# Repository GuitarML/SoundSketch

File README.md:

# SoundSketch

Hardware and software for Soundsketch guitar pedal as shown on [Youtube](https://youtu.be/grorq3XL0zQ?si=FIOID7Fv4AuRCGD6)

Borrows from the open source [DaisySeedProjects](https://github.com/bkshepherd/DaisySeedProjects) pedal, but expression and 3 way toggles, and screen/encoder, midi out removed. 

Not all of the Planet Series software modules ported from Funbox have been tested, some code editing may be required. 

IMPORTANT: When ordering assembled Soundsketch PCBs from JLCPcb or PCBway, you have to manually rotate certain components to the correct orientation on their online tool as part of the ordering process. This is required because the part data exported from KiCad to the .pos file is a different standard from what is expected by the manufacturer. Use the KiCad PCB view to verify correct orientation of ICs and diodes when compared to the manufacturer's parts visualization tool. 

Tayda Drill Template:
https://drill.taydakits.com/box-designs/new?public_key=MndaazFjcjJRM3hIUVQxenhPUm1Rdz09Cg==

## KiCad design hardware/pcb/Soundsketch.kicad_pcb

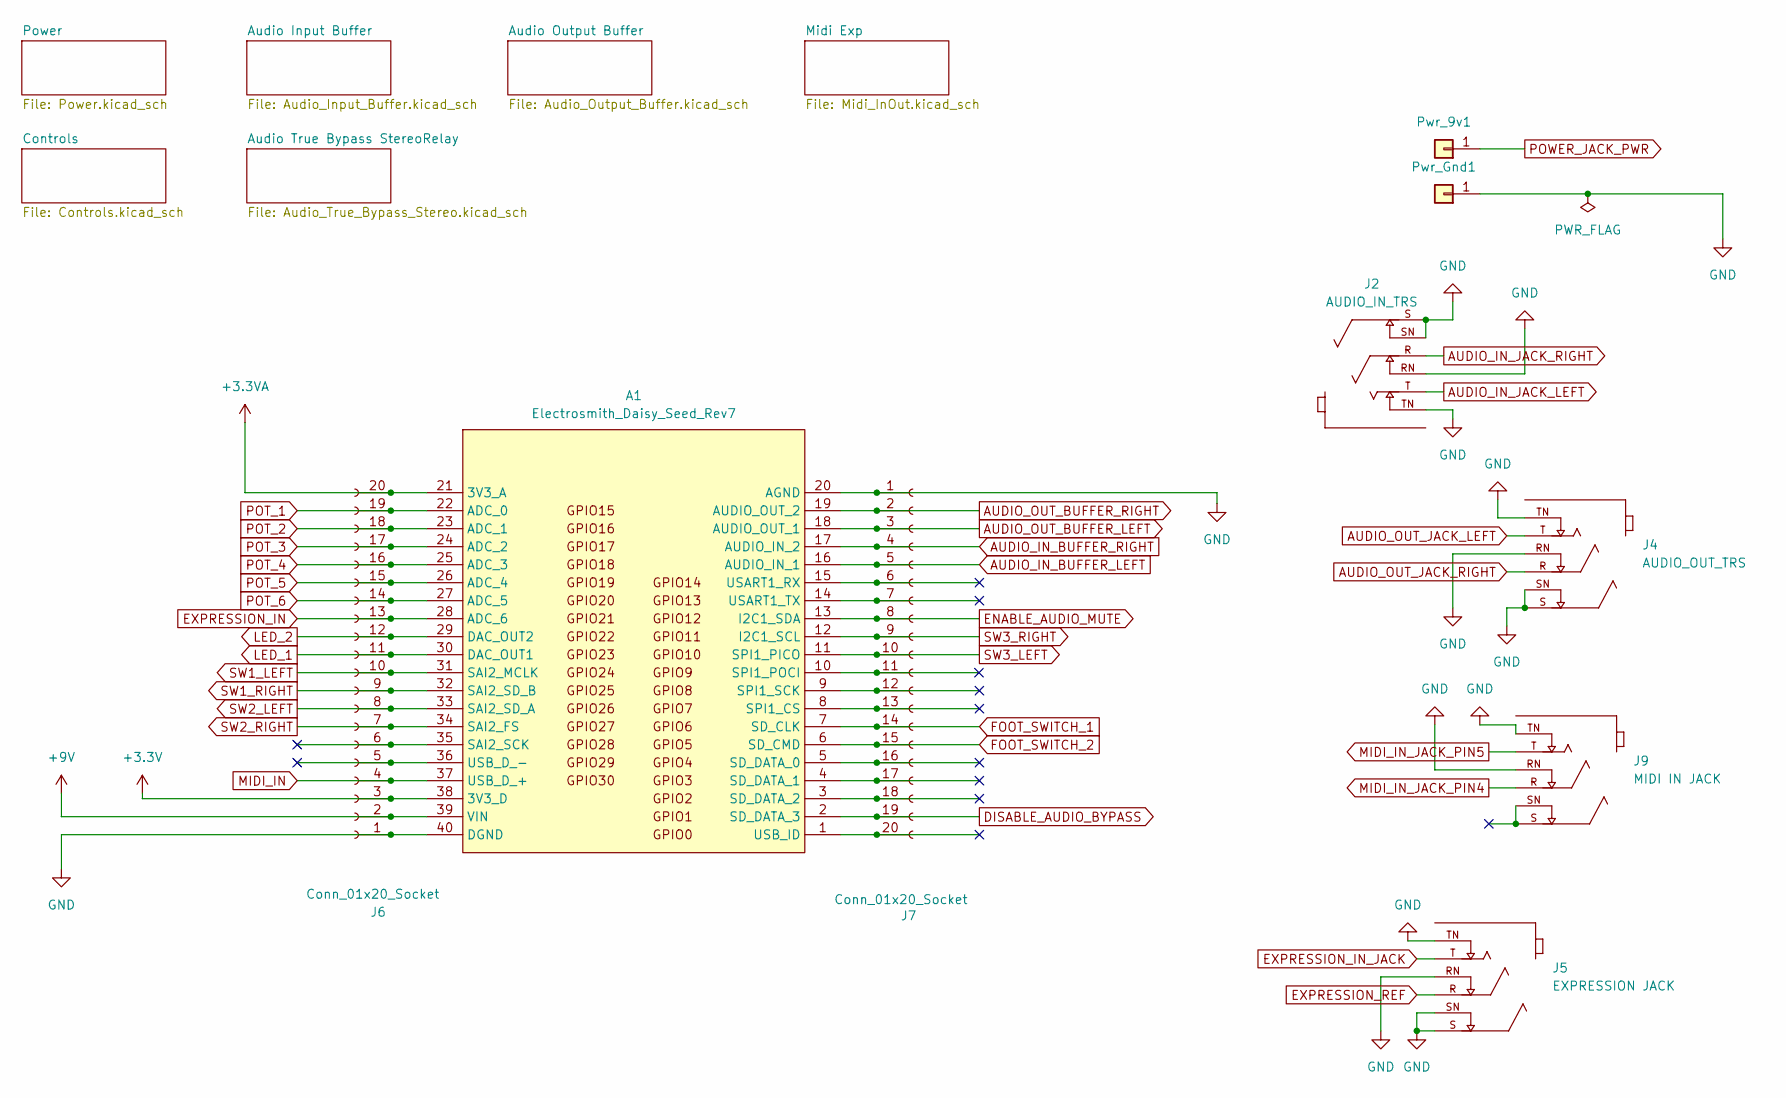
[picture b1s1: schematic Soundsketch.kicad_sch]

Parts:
A1: Electrosmith_Daisy_Seed_Rev7
J2: AUDIO_IN_TRS; NEUTRIK_NMJ6HCD2; PARTREV 26.02.2021
J4: AUDIO_OUT_TRS; NEUTRIK_NMJ6HCD2; PARTREV 26.02.2021
J5: EXPRESSION JACK; NEUTRIK_NMJ6HCD2; PARTREV 26.02.2021
J6, J7: Conn_01x20_Socket; PinSocket1x20_P2.54mm_Vertical_JLCPCB
J9: MIDI IN JACK; NEUTRIK_NMJ6HCD2; PARTREV 26.02.2021
Pwr_9v1: TestPoint_THTPad_D2.0mm_Drill1.0mm
Pwr_Gnd1: TestPoint_THTPad_D2.0mm_Drill1.0mm

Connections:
+3.3V: A1.38 (3V3_D), J6.3; also elsewhere on the board
+3.3VA: A1.21 (3V3_A), J6.20; also elsewhere on the board
+9V: A1.39 (VIN), J6.2; also elsewhere on the board
AUDIO_IN_BUFFER_LEFT: A1.16 (AUDIO_IN_1), J7.5; also elsewhere on the board
AUDIO_IN_BUFFER_RIGHT: A1.17 (AUDIO_IN_2), J7.4; also elsewhere on the board
AUDIO_IN_JACK_LEFT: J2.T; also elsewhere on the board
AUDIO_IN_JACK_RIGHT: J2.R; also elsewhere on the board
AUDIO_OUT_BUFFER_LEFT: A1.18 (AUDIO_OUT_1), J7.3; also elsewhere on the board
AUDIO_OUT_BUFFER_RIGHT: A1.19 (AUDIO_OUT_2), J7.2; also elsewhere on the board
AUDIO_OUT_JACK_LEFT: J4.T; also elsewhere on the board
AUDIO_OUT_JACK_RIGHT: J4.R; also elsewhere on the board
DISABLE_AUDIO_BYPASS: A1.2 (SD_DATA_3), J7.19; also elsewhere on the board
ENABLE_AUDIO_MUTE: A1.13 (I2C1_SDA), J7.8; also elsewhere on the board
EXPRESSION_IN: A1.28 (ADC_6), J6.13; also elsewhere on the board
EXPRESSION_IN_JACK: J5.T; also elsewhere on the board
EXPRESSION_REF: J5.R; also elsewhere on the board
FOOT_SWITCH_1: A1.7 (SD_CLK), J7.14; also elsewhere on the board
FOOT_SWITCH_2: A1.6 (SD_CMD), J7.15; also elsewhere on the board
GND: A1.20 (AGND), A1.40 (DGND), J2.RN, J2.S, J2.SN, J2.TN, J4.RN, J4.S, J4.SN, J4.TN, J5.RN, J5.S, J5.SN, J5.TN, J6.1, J7.1, J9.RN, J9.TN, Pwr_Gnd1.1; also elsewhere on the board
LED_1: A1.30 (DAC_OUT1), J6.11; also elsewhere on the board
LED_2: A1.29 (DAC_OUT2), J6.12; also elsewhere on the board
MIDI_IN: A1.37 (USB_D_+), J6.4; also elsewhere on the board
MIDI_IN_JACK_PIN4: J9.R; also elsewhere on the board
MIDI_IN_JACK_PIN5: J9.T; also elsewhere on the board
unnamed: A1.1 (USB_ID), J7.20
unnamed: A1.3 (SD_DATA_2), J7.18
unnamed: A1.4 (SD_DATA_1), J7.17
unnamed: A1.5 (SD_DATA_0), J7.16
unnamed: A1.8 (SPI1_CS), J7.13
unnamed: A1.9 (SPI1_SCK), J7.12
unnamed: A1.14 (USART1_TX), J7.7
unnamed: A1.15 (USART1_RX), J7.6
unnamed: A1.35 (SAI2_SCK), J6.6
unnamed: A1.36 (USB_D_-), J6.5
unnamed: A1.10 (SPI1_POCI), J7.11
POT_1: A1.22 (ADC_0), J6.19; also elsewhere on the board
POT_2: A1.23 (ADC_1), J6.18; also elsewhere on the board
POT_3: A1.24 (ADC_2), J6.17; also elsewhere on the board
POT_4: A1.25 (ADC_3), J6.16; also elsewhere on the board
POT_5: A1.26 (ADC_4), J6.15; also elsewhere on the board
POT_6: A1.27 (ADC_5), J6.14; also elsewhere on the board
POWER_JACK_PWR: Pwr_9v1.1; also elsewhere on the board
SW1_LEFT: A1.31 (SAI2_MCLK), J6.10; also elsewhere on the board
SW1_RIGHT: A1.32 (SAI2_SD_B), J6.9; also elsewhere on the board
SW2_LEFT: A1.33 (SAI2_SD_A), J6.8; also elsewhere on the board
SW2_RIGHT: A1.34 (SAI2_FS), J6.7; also elsewhere on the board
SW3_LEFT: A1.11 (SPI1_PICO), J7.10; also elsewhere on the board
SW3_RIGHT: A1.12 (I2C1_SCL), J7.9; also elsewhere on the board

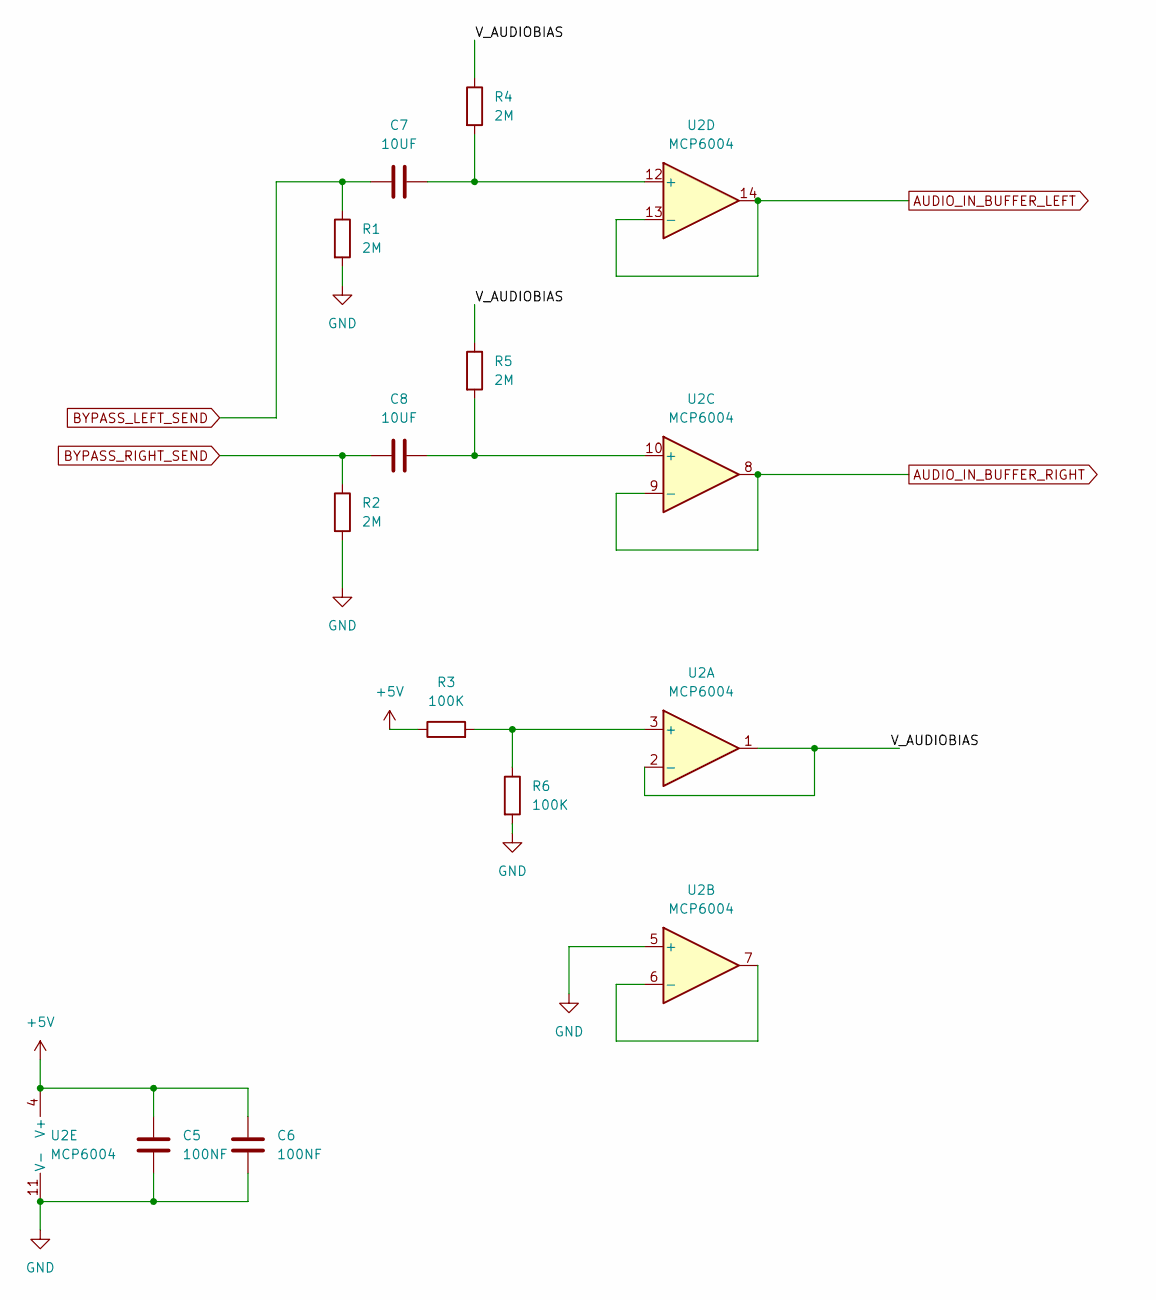
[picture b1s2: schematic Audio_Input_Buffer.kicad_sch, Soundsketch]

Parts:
C5, C6: 100NF; C_0805_2012Metric
C7, C8: 10UF; C_0805_2012Metric
R1, R2, R4, R5: 2M; R_0805_2012Metric
R3, R6: 100K; R_0805_2012Metric
U2: MCP6004; SOIC-14_3.9x8.7mm_P1.27mm

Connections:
+5V: C5.1, C6.1, R3.1, U2.4 (V+); also elsewhere on the board
/Audio Input Buffer/V_AUDIOBIAS: R4.1, R5.1, U2.1, U2.2 (-)
AUDIO_IN_BUFFER_LEFT: U2.13 (-), U2.14; also elsewhere on the board
AUDIO_IN_BUFFER_RIGHT: U2.8, U2.9 (-); also elsewhere on the board
BYPASS_LEFT_SEND: C7.1, R1.1; also elsewhere on the board
BYPASS_RIGHT_SEND: C8.1, R2.1; also elsewhere on the board
GND: C5.2, C6.2, R1.2, R2.2, R6.2, U2.5 (+), U2.11 (V-); also elsewhere on the board
unnamed: R3.2, R6.1, U2.3 (+)
unnamed: U2.6 (-), U2.7
unnamed: C8.2, R5.2, U2.10 (+)
unnamed: C7.2, R4.2, U2.12 (+)

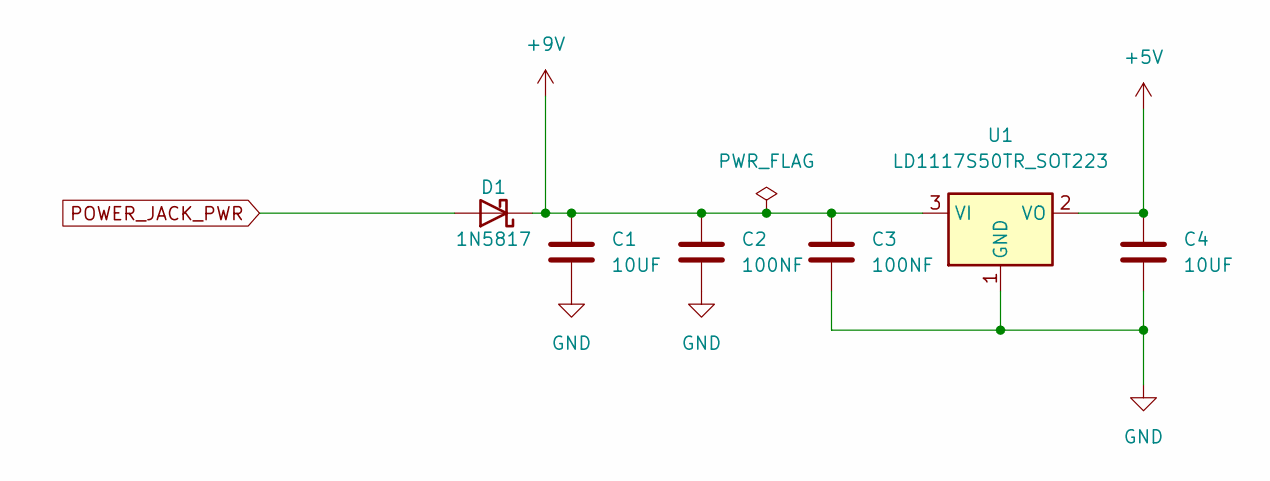
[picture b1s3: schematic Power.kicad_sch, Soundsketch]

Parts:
C1, C4: 10UF; C_0805_2012Metric
C2, C3: 100NF; C_0805_2012Metric
D1: 1N5817; D_SOD-123
U1: LD1117S50TR_SOT223; SOT-223-3_TabPin2

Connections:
+5V: C4.1, U1.2 (VO); also elsewhere on the board
+9V: C1.1, C2.1, C3.1, D1.1 (K), U1.3 (VI); also elsewhere on the board
GND: C1.2, C2.2, C3.2, C4.2, U1.1 (GND); also elsewhere on the board
POWER_JACK_PWR: D1.2 (A); also elsewhere on the board

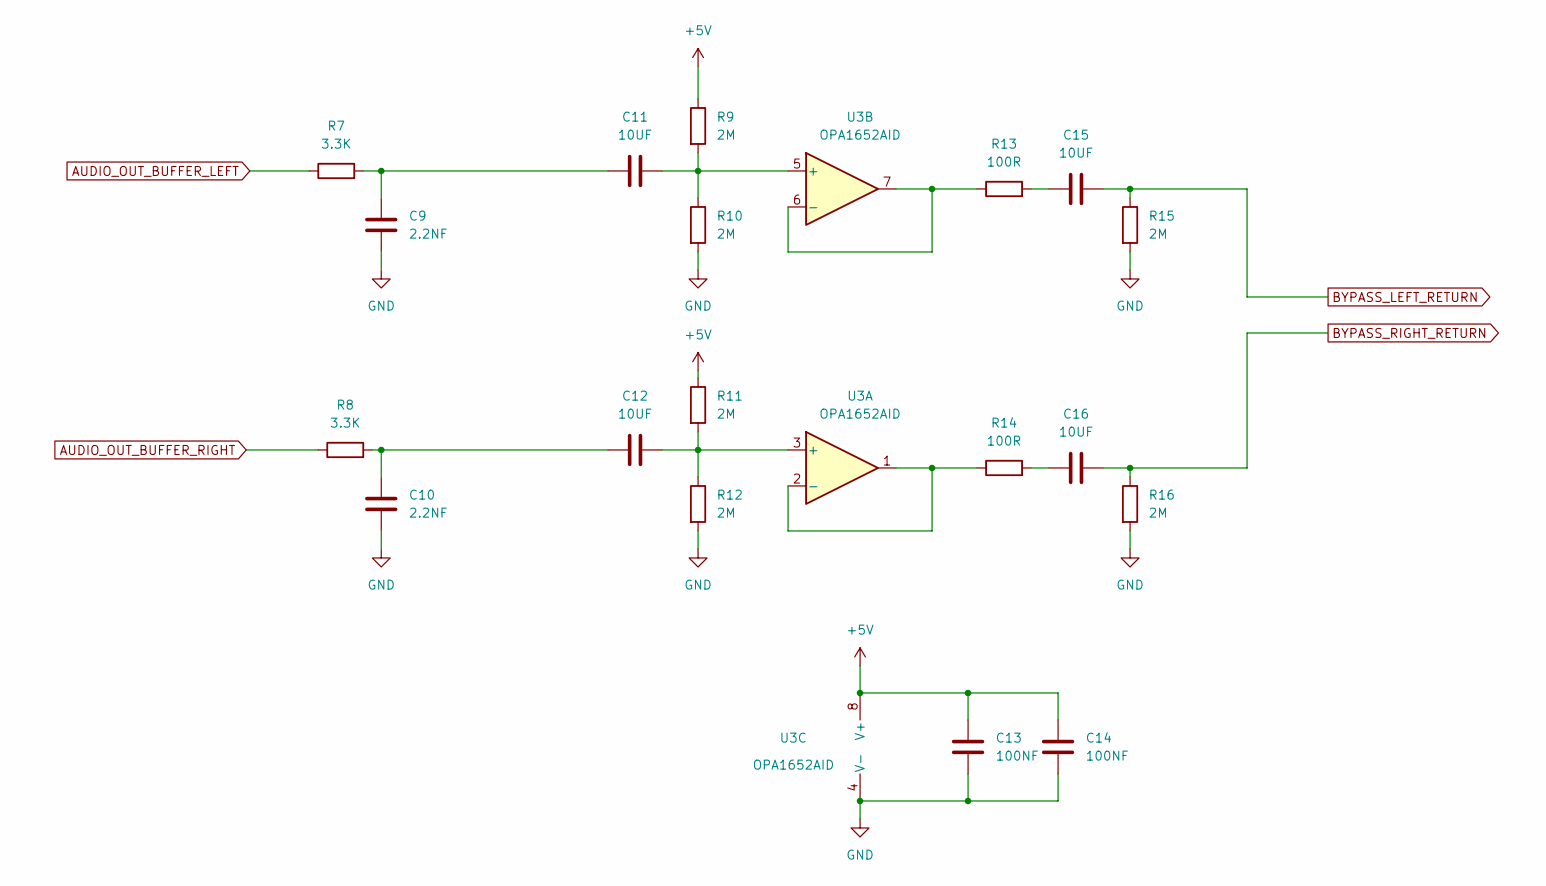
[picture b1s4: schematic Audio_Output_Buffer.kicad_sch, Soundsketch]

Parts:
C9, C10: 2.2NF; C_0805_2012Metric
C11, C12, C15, C16: 10UF; C_0805_2012Metric
C13, C14: 100NF; C_0805_2012Metric
R7, R8: 3.3K; R_0805_2012Metric
R9, R10, R11, R12, R15, R16: 2M; R_0805_2012Metric
R13, R14: 100R; R_0805_2012Metric
U3: OPA1652AID; SOIC-8_3.9x4.9mm_P1.27mm

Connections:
+5V: C13.1, C14.1, R9.1, R11.1, U3.8 (V+); also elsewhere on the board
AUDIO_OUT_BUFFER_LEFT: R7.1; also elsewhere on the board
AUDIO_OUT_BUFFER_RIGHT: R8.1; also elsewhere on the board
BYPASS_LEFT_RETURN: C15.2, R15.1; also elsewhere on the board
BYPASS_RIGHT_RETURN: C16.2, R16.1; also elsewhere on the board
GND: C9.2, C10.2, C13.2, C14.2, R10.2, R12.2, R15.2, R16.2, U3.4 (V-); also elsewhere on the board
unnamed: C10.1, C12.2, R8.2
unnamed: C9.1, C11.2, R7.2
unnamed: C15.1, R13.2
unnamed: C16.1, R14.2
unnamed: C12.1, R11.2, R12.1, U3.3 (+)
unnamed: R14.1, U3.1, U3.2 (-)
unnamed: C11.1, R9.2, R10.1, U3.5 (+)
unnamed: R13.1, U3.6 (-), U3.7

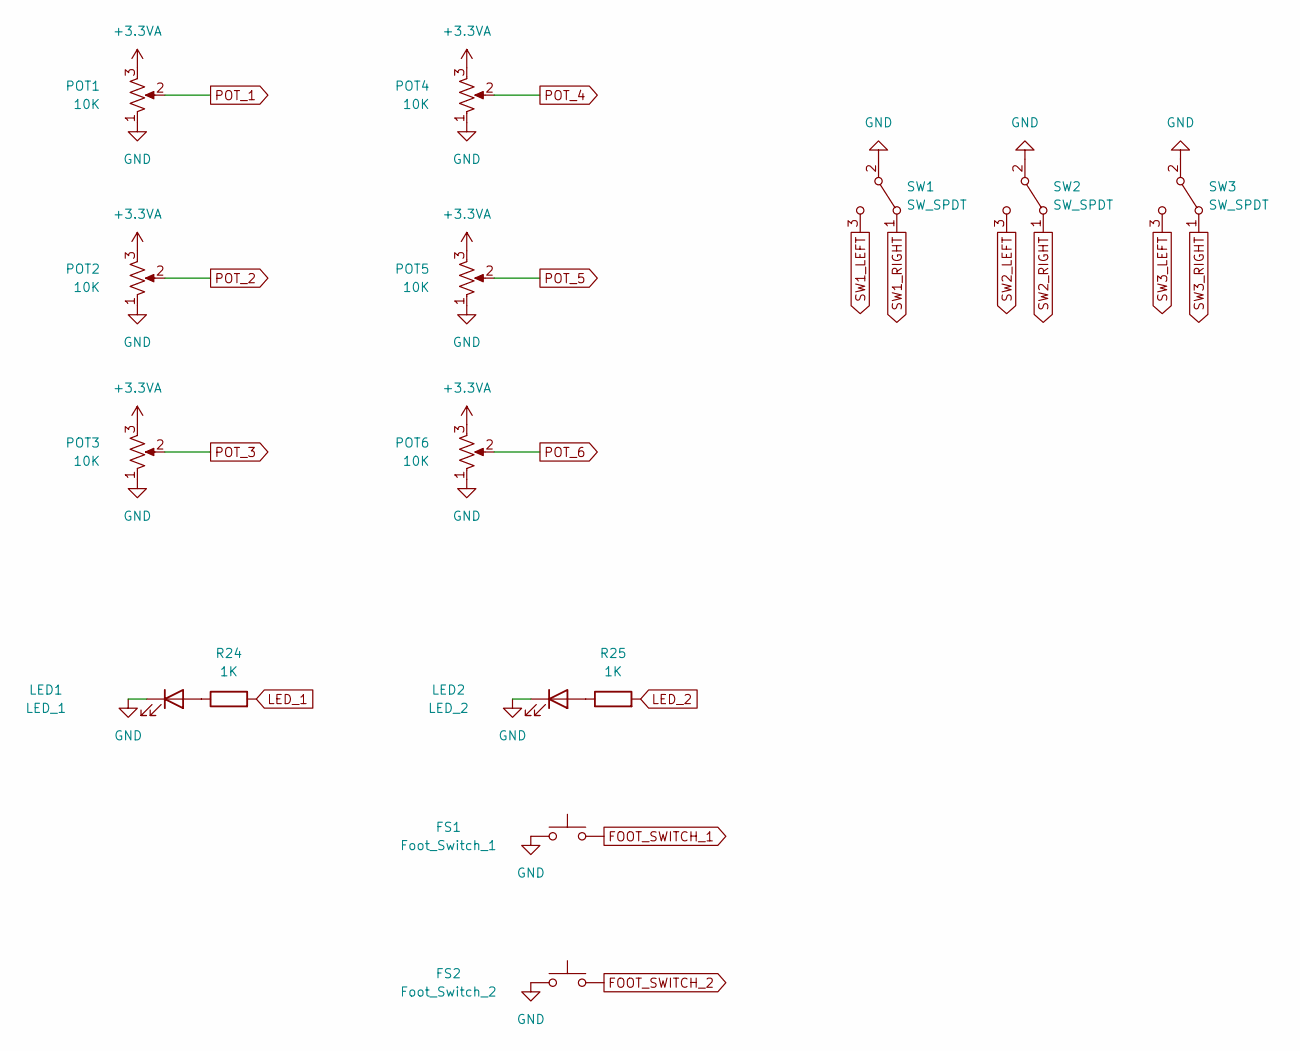
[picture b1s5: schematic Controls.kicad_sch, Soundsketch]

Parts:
FS1: Foot_Switch_1; PinHeader_1x02_P2.54mm_Vertical
FS2: Foot_Switch_2; PinHeader_1x02_P2.54mm_Vertical
LED1: LED_1; PinHeader_1x02_P2.54mm_Vertical
LED2: LED_2; PinHeader_1x02_P2.54mm_Vertical
POT1, POT2, POT3, POT4, POT5, POT6: 10K; Pot_RightAngle_LongPin_16mm
R24, R25: 1K; R_0805_2012Metric
SW1, SW2, SW3: SW_SPDT; SW_Toggle_SPDT_lugs

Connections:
+3.3VA: POT1.3, POT2.3, POT3.3, POT4.3, POT5.3, POT6.3; also elsewhere on the board
FOOT_SWITCH_1: FS1.2; also elsewhere on the board
FOOT_SWITCH_2: FS2.2; also elsewhere on the board
GND: FS1.1, FS2.1, LED1.1 (K), LED2.1 (K), POT1.1, POT2.1, POT3.1, POT4.1, POT5.1, POT6.1, SW1.2 (B), SW2.2 (B), SW3.2 (B); also elsewhere on the board
LED_1: R24.2; also elsewhere on the board
LED_2: R25.2; also elsewhere on the board
unnamed: LED1.2 (A), R24.1
unnamed: LED2.2 (A), R25.1
POT_1: POT1.2; also elsewhere on the board
POT_2: POT2.2; also elsewhere on the board
POT_3: POT3.2; also elsewhere on the board
POT_4: POT4.2; also elsewhere on the board
POT_5: POT5.2; also elsewhere on the board
POT_6: POT6.2; also elsewhere on the board
SW1_LEFT: SW1.3 (C); also elsewhere on the board
SW1_RIGHT: SW1.1 (A); also elsewhere on the board
SW2_LEFT: SW2.3 (C); also elsewhere on the board
SW2_RIGHT: SW2.1 (A); also elsewhere on the board
SW3_LEFT: SW3.3 (C); also elsewhere on the board
SW3_RIGHT: SW3.1 (A); also elsewhere on the board

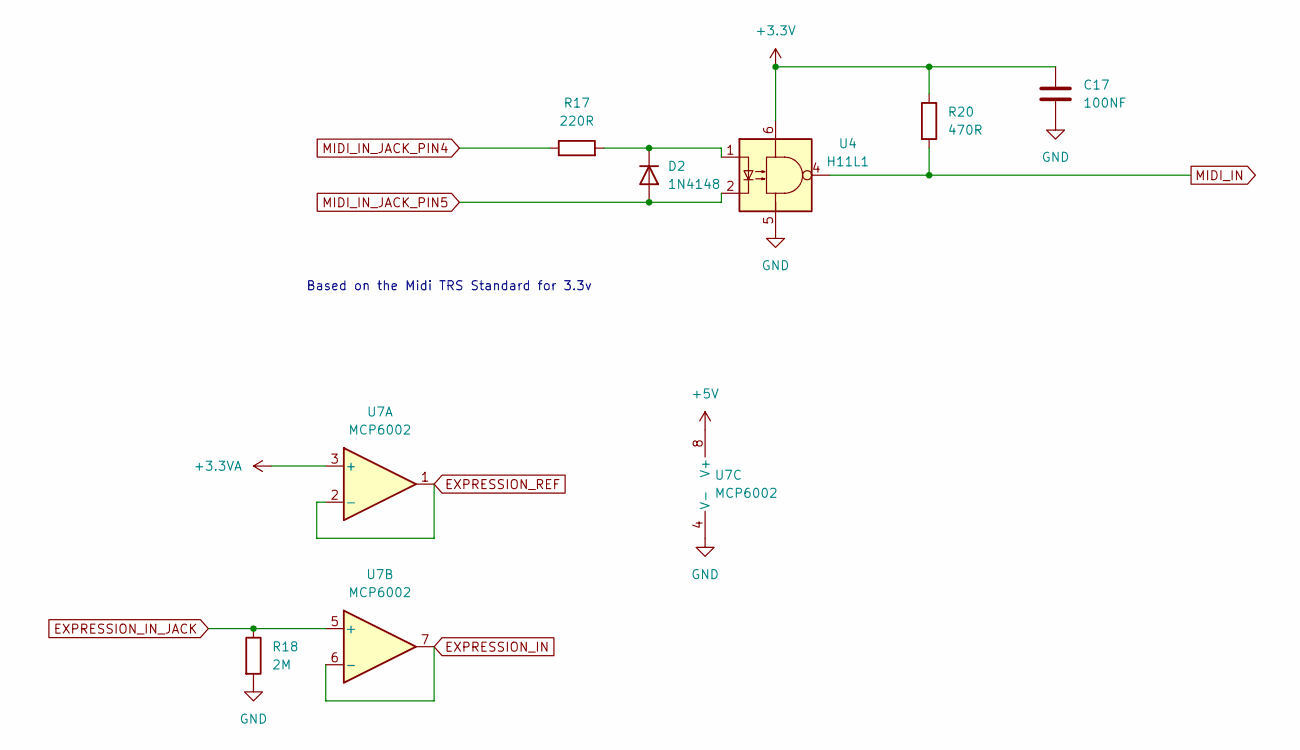
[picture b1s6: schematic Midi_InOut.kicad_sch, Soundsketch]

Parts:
C17: 100NF; C_0805_2012Metric
D2: 1N4148; D_SOD-123
R17: 220R; R_0805_2012Metric
R18: 2M; R_0805_2012Metric
R20: 470R; R_0805_2012Metric
U4: H11L1; SOP-6_2.54mm
U7: MCP6002; SOIC-8_3.9x4.9mm_P1.27mm

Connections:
+3.3V: C17.1, R20.1, U4.6; also elsewhere on the board
+3.3VA: U7.3 (+); also elsewhere on the board
+5V: U7.8 (V+); also elsewhere on the board
EXPRESSION_IN: U7.6 (-), U7.7; also elsewhere on the board
EXPRESSION_IN_JACK: R18.1, U7.5 (+); also elsewhere on the board
EXPRESSION_REF: U7.1, U7.2 (-); also elsewhere on the board
GND: C17.2, R18.2, U4.5, U7.4 (V-); also elsewhere on the board
MIDI_IN: R20.2, U4.4; also elsewhere on the board
MIDI_IN_JACK_PIN4: R17.1; also elsewhere on the board
MIDI_IN_JACK_PIN5: D2.2 (A), U4.2; also elsewhere on the board
unnamed: D2.1 (K), R17.2, U4.1

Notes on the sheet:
Based on the Midi TRS Standard for 3.3v

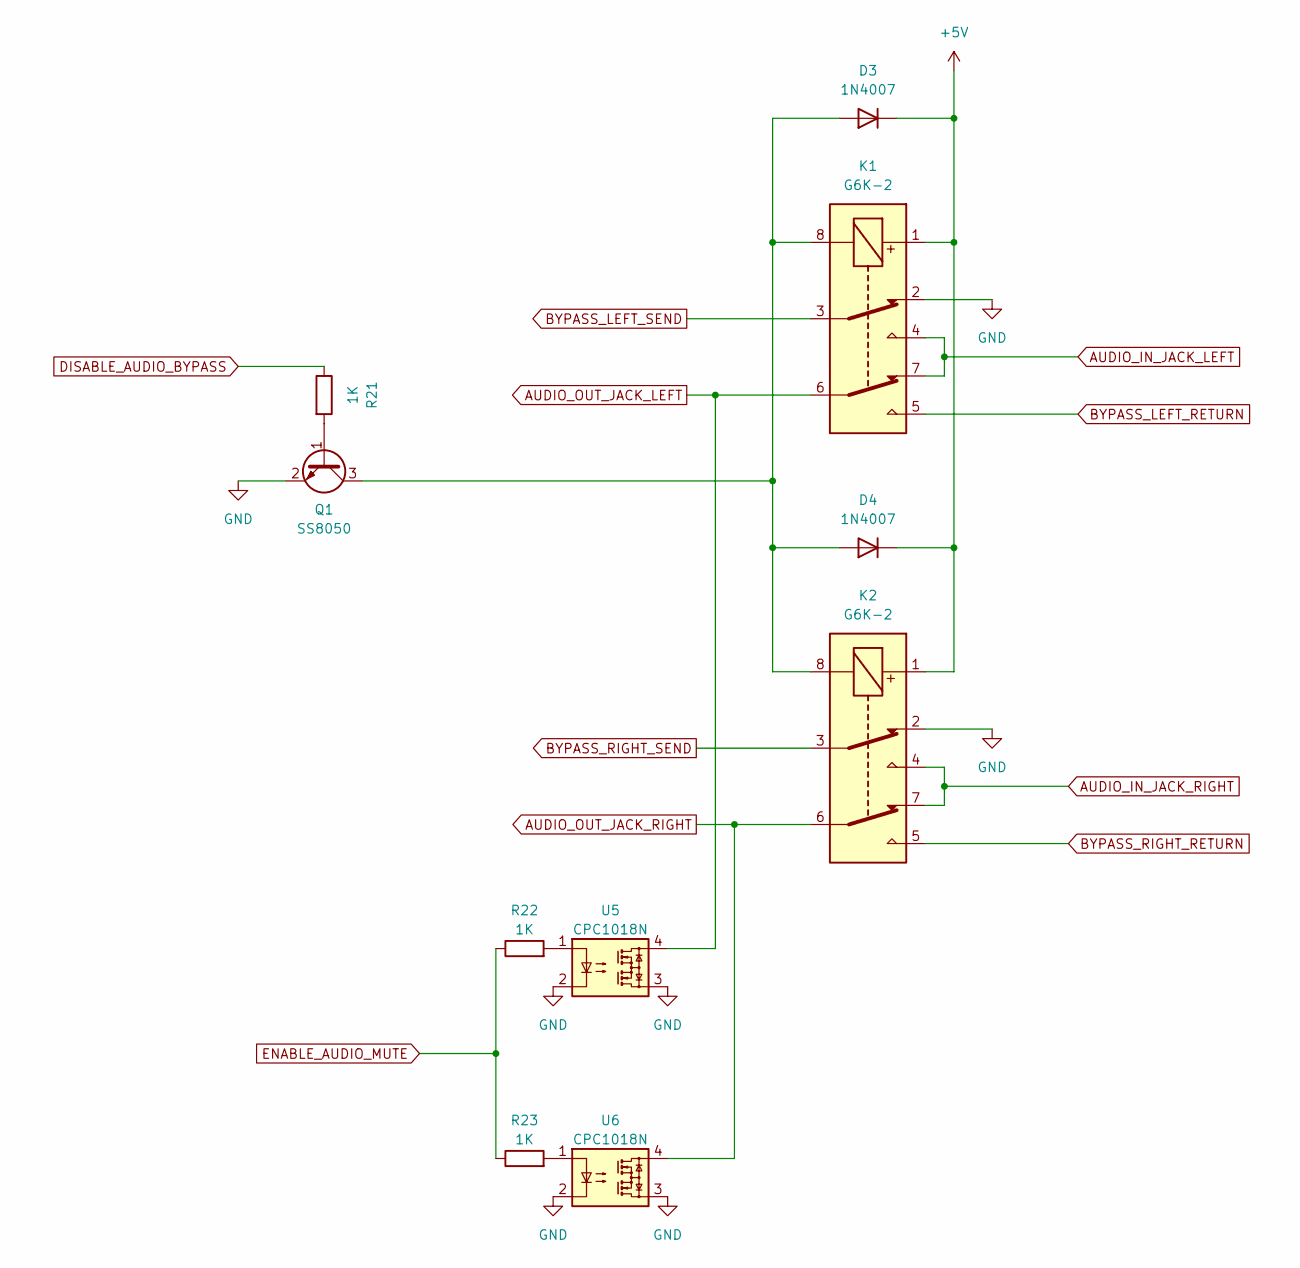
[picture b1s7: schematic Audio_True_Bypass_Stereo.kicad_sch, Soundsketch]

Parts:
D3, D4: 1N4007; D_SOD-123F
K1, K2: G6K-2; Relay_DPDT_Omron_G6K-2G-Y
Q1: SS8050; SOT-23-3
R21, R22, R23: 1K; R_0805_2012Metric
U5, U6: CPC1018N; SOP-4_3.8x4.1mm_P2.54mm

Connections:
+5V: D3.1 (K), D4.1 (K), K1.1, K2.1; also elsewhere on the board
AUDIO_IN_JACK_LEFT: K1.4, K1.7; also elsewhere on the board
AUDIO_IN_JACK_RIGHT: K2.4, K2.7; also elsewhere on the board
AUDIO_OUT_JACK_LEFT: K1.6, U5.4; also elsewhere on the board
AUDIO_OUT_JACK_RIGHT: K2.6, U6.4; also elsewhere on the board
BYPASS_LEFT_RETURN: K1.5; also elsewhere on the board
BYPASS_LEFT_SEND: K1.3; also elsewhere on the board
BYPASS_RIGHT_RETURN: K2.5; also elsewhere on the board
BYPASS_RIGHT_SEND: K2.3; also elsewhere on the board
DISABLE_AUDIO_BYPASS: R21.1; also elsewhere on the board
ENABLE_AUDIO_MUTE: R22.1, R23.1; also elsewhere on the board
GND: K1.2, K2.2, Q1.2 (E), U5.2, U5.3, U6.2, U6.3; also elsewhere on the board
unnamed: D3.2 (A), D4.2 (A), K1.8, K2.8, Q1.3 (C)
unnamed: Q1.1 (B), R21.2
unnamed: R22.2, U5.1
unnamed: R23.2, U6.1

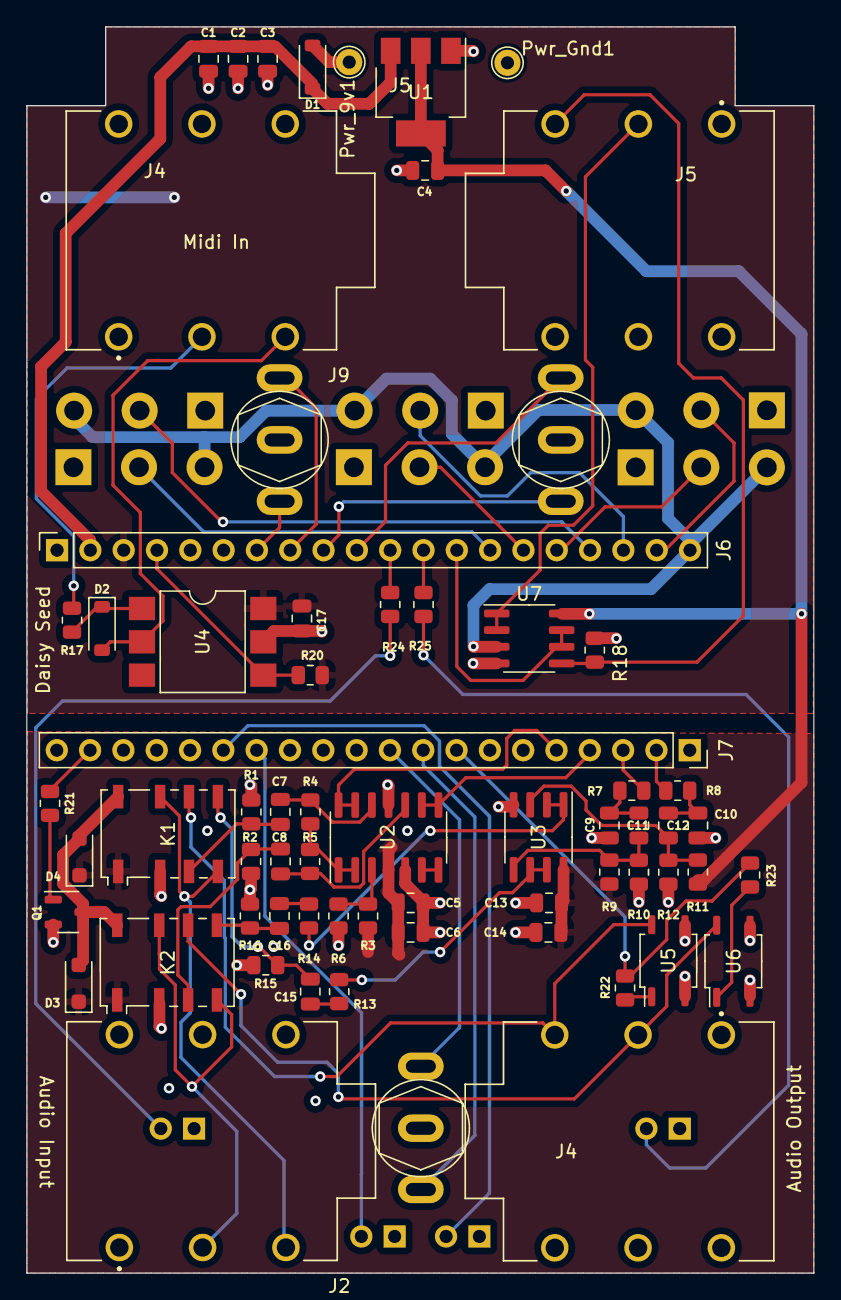
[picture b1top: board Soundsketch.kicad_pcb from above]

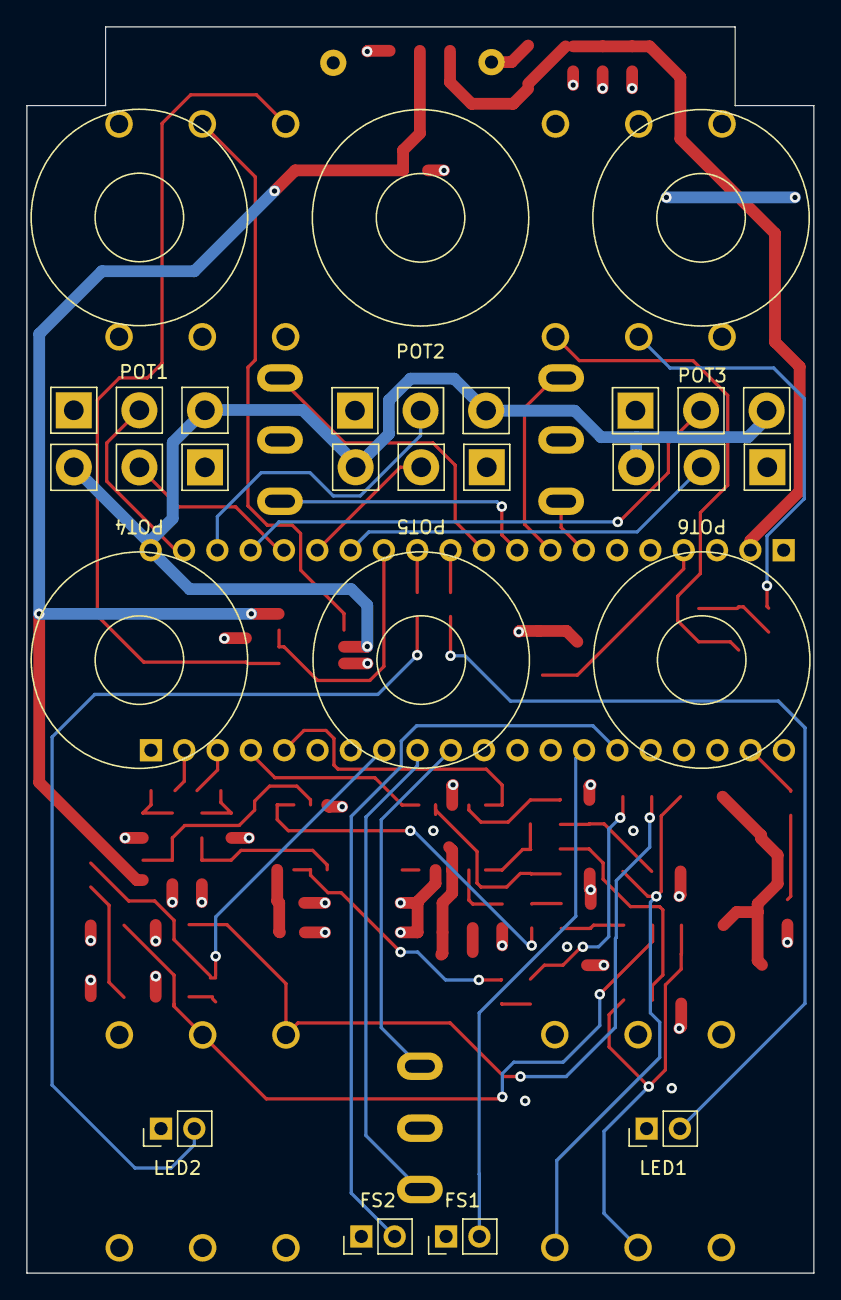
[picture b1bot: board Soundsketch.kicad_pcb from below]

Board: 4 copper layers, 60.0 x 95.0 mm, 76 parts (10 on the bottom side), 62 nets.

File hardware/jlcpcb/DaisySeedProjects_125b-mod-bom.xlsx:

Comment | Designator | Footprint | JLCPCB Part #（optional）
H11L1 | U4 | SOP-6_2.54mm | C78589
470R | R20 | 805 | C17710
1x20 Through Hole Header | J7,J6 |  | C50984
2M | R11,R1,R2,R12,R5,R10,R15,R18,R16,R4,R9 | 805 | C26112
G6K-2G-Y DC5 | K2,K1 | SMD,6.5x10mm | C397140
OPA1652AIDR | U3 | SOIC-8 | C30025
MCP6004T-I/SL | U2 | SOIC-14 | C7378
100R | R14,R13 | 805 | C17408
2.2NF | C10,C9 | 805 | C28260
10UF | C1,C8,C7,C12,C4,C11,C16,C15 | 805 | C15850
1K | R23,R22,R21,R25,R24 | 805 | C17513
1N4007W | D3,D4 | SOD-123FL | C108803
3.3K | R7,R8 | 805 | C26010
100NF | C14,C13,C3,C2,C6,C17,C5 | 805 | C49678
MCP6002T-I/SN | U7 | SOIC-8 | C7377
CPC1018N | U5,U6 | SOP-4-2.54mm | C133069
100K | R3,R6 | 805 | C149504
1N4148W | D2 | SOD-123 | C81598
NMJ6HCD2 | J2, J4, J5, J9 |  | C368502
LD1117S50CTR | U1 | SOT-223-3 | C81157
220R | R17 | 805 | C17557
1N5817 | D1 | SOD-123 | C727113
SS8050 | Q1 | SOT-23-3 | C2150

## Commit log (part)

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2025-07-10 Added dependencies
2025-07-11 Updated makefiles with new dependency path
2025-07-11 Updated uranus and neptune
2025-07-12 Fixed alternate mode for uranus
